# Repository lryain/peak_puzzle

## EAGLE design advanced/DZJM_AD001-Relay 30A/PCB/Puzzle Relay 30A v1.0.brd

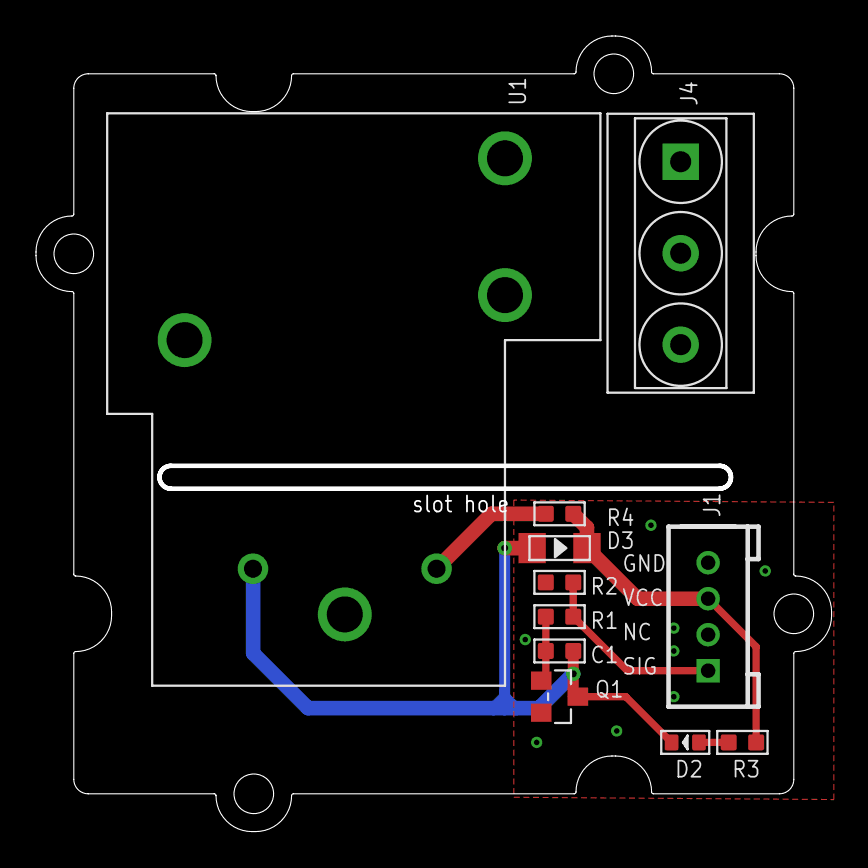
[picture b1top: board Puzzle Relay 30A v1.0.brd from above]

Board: 2 copper layers, 44.2 x 44.2 mm, 14 parts (1 on the bottom side), 10 nets.

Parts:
C1: 100pF; C0603
D2: Green; LED-0603
D3: LL4148; DO-35-SMD
J1: 4P-2.0
J4: 3P-5.08
Q1: S9013; SOT23
R1: 2k; R0603
R2: 10K; R0603
R3: 1K; R0603
R4: 10; R0603
U1: 6P-19.8H
U$3: 2X2U-DIM-W/-DRILL
U$4: OSHW_FILLX200_NOTEXT
U$6: BRICK-LOGO-2-B-MIL-0.3

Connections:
COM: J4.3, U1.4
GND: J1.4, Q1.2, R2.1
unnamed: C1.1, Q1.1, R1.2
unnamed: D2.+, R3.2
unnamed: C1.2, D2.-, D3.A, Q1.3, U1.3
unnamed: R4.2, U1.1
NC: J4.1, U1.5
NO: J4.2, U1.6
SIG: J1.1, R1.1, R2.2
VCC: D3.C, J1.3, R3.1, R4.1

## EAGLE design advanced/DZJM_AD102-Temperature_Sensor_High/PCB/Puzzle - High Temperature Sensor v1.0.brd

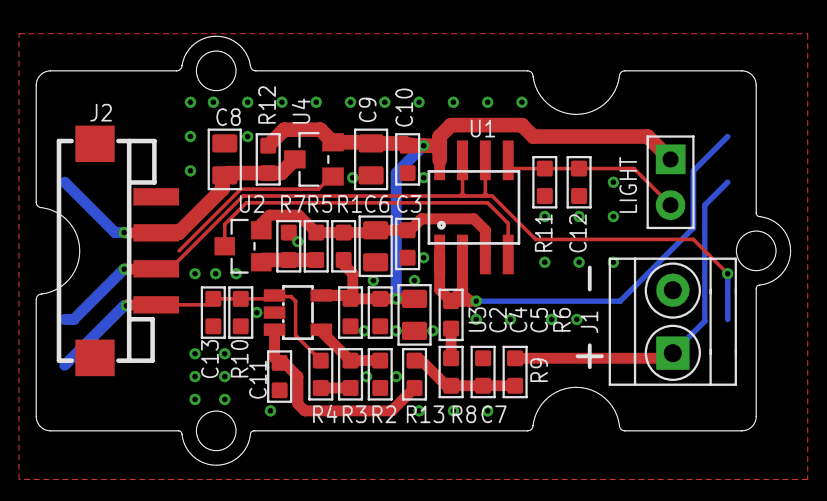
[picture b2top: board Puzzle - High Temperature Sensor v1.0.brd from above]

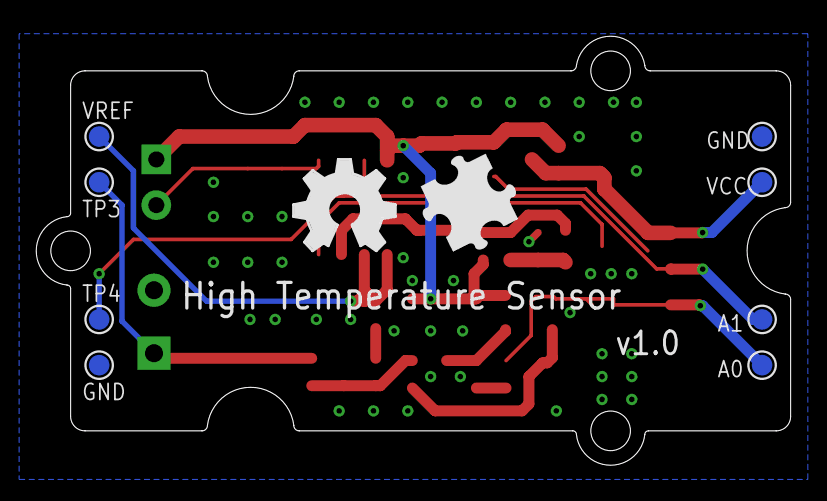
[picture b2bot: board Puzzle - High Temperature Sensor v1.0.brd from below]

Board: 2 copper layers, 41.9 x 23.8 mm, 43 parts (10 on the bottom side), 15 nets.

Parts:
A0, A1: TP3; TP_4545
C2, C3, C4, C7, C10: 100nF; C0603
C5, C6, C8, C9: 10uF/25v; C0805
C11: DNP; C0603
C12, C13: 1nF; C0603
J1: 2P-3.5
J2: Grove con; 4P-SMD-2.0
LIGHT: TTC3A103*39H; CK_1*2
R1: 330R; R0603
R2, R9: 1K_1%; R0603
R3: 51K_1%; R0603
R4: 2.4K_1%; R0603
R5: 2K_1%; R0603
R6: 150K_1%; R0603
R7, R11: 10K_1%; R0603
R8: 82K_1%; R0603
R10: 10K; R0603
R12: DNP; R0603
R13: 0R; R0603
TP, TP2, TP3, TP4: TP_4545
U1: LMV358D; SO08
U2: CJ432; SOT23
U3: OPA333DBV; SOT23-5
U4: XC6206P332MR-G; SOT23
U$9: GROVE-2CONNECTOR-SMD
U$11: BRICK-LOGO-MIL-0.6
U$12: OSHW_FILLX200_NOTEXT
VCC: TP2; TP_4545
VREF: TP4; TP_4545

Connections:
1V5: R6.2, U1.1, U1.2, VREF.T
A0: A0.T, C13.2, J2.1, R4.1, R10.2, U3.1
A1: A1.T, J2.2, TP4.T, U1.6, U1.7
GND: C2.1, C3.1, C4.1, C5.1, C6.1, C7.1, C8.1, C9.1, C10.1, C11.1, C12.1, C13.1, J1.2, J2.4, J2.SS1, J2.SS2, R2.2, R7.2, R10.1, R11.1, TP.T, TP2.T, U1.4, U2.3, U3.2, U4.1
unnamed: C7.2, R8.1, R9.2, R13.2
unnamed: R2.1, R3.2, U3.4
unnamed: J1.1, R9.1, TP3.T
unnamed: R3.1, R4.2
unnamed: C12.2, LIGHT.2, R11.2, U1.5
unnamed: R6.1, R8.2
unnamed: C11.2, R13.1, U3.3
unnamed: R5.2, R7.1, U2.1
VCC: C8.2, J2.3, R12.1, U4.3, VCC.T
VCC_3V3: C2.2, C4.2, C5.2, C9.2, C10.2, LIGHT.1, R1.1, R12.2, U1.8, U3.5, U4.2
VREF: C3.2, C6.2, R1.2, R5.1, U1.3, U2.2

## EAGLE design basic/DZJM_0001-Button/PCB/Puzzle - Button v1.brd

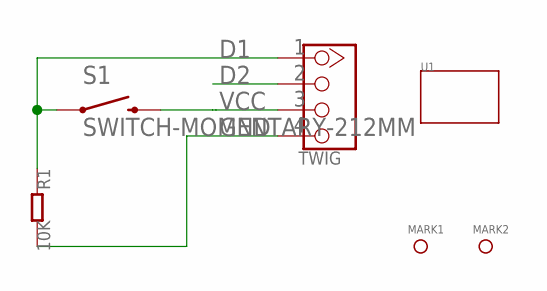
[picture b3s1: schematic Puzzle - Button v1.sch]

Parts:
J1: TWIG; 4P-LEADED-2.0
MARK1, MARK2: PAD-MARK; ROUND-MARK-0.635
R1: 10K; 0603
S1: SWITCH-MOMENTARY-212MM; TACTILE-PTH-12MM
U1: TWIG-1U; 1U-DIM-W/-DRILL

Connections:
D1: J1.1, R1.1, S1.1
D2: J1.2
GND: J1.4, R1.2
VCC: J1.3, S1.3 (2)

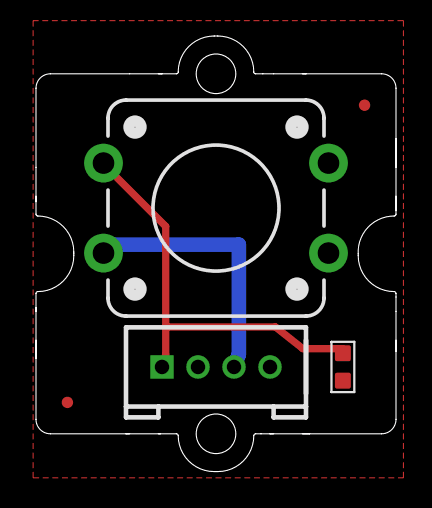
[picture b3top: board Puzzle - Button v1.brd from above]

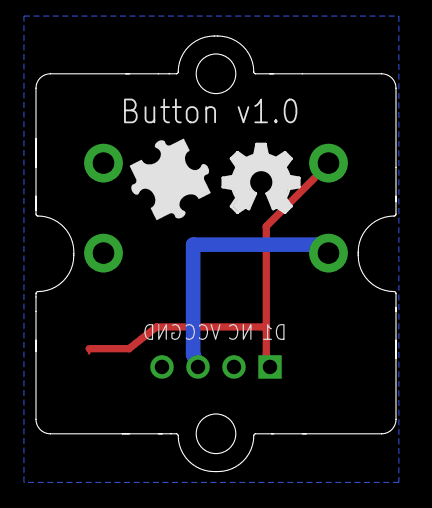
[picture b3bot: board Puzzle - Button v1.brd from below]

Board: 2 copper layers, 20.0 x 24.2 mm, 8 parts (2 on the bottom side), 3 nets.

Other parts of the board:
LOGO2: LOGO-OSHW-FILLX0150-NT; OSHW_FILLX150_NOTEXT
U$1: BRICK-LOGO-MIL-0.5

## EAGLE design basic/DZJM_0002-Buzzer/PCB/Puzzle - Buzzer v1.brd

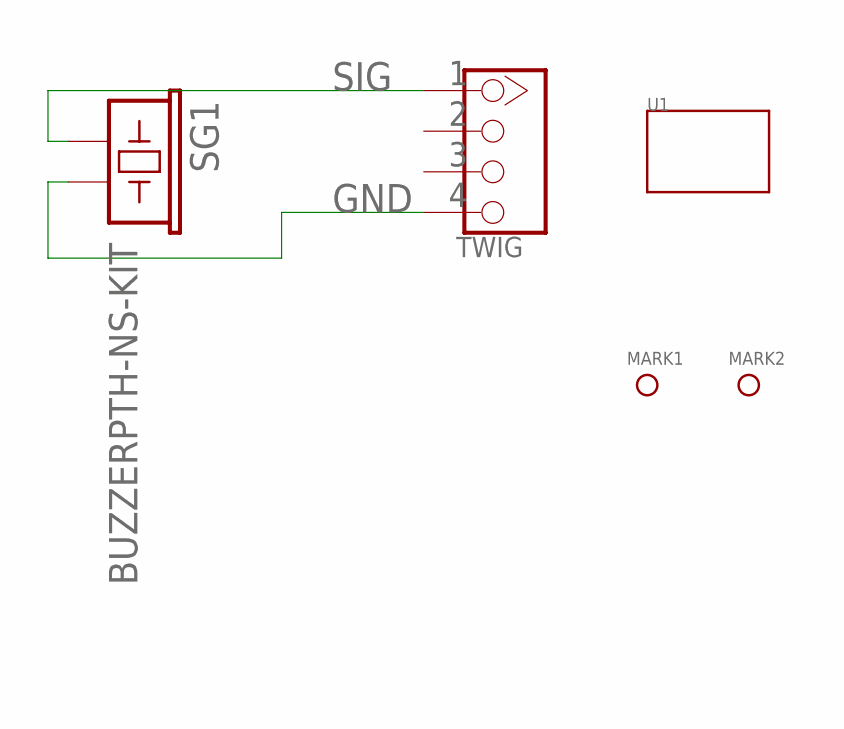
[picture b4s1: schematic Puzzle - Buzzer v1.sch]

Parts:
J1: TWIG; 4P-LEADED-2.0
MARK1, MARK2: PAD-MARK; ROUND-MARK-0.635
SG1: BUZZERPTH-NS-KIT; BUZZER-12MM-NS-KIT
U1: TWIG-1U; 1U-DIM-W/-DRILL

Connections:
GND: J1.4, SG1.- (2)
SIG: J1.1, SG1.+ (1)

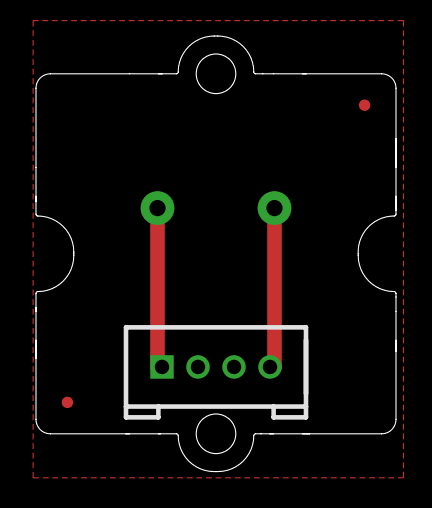
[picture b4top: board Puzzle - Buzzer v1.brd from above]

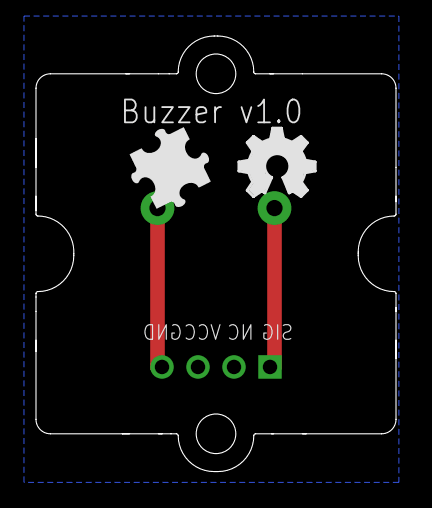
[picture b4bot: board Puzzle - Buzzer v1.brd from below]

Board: 2 copper layers, 20.0 x 24.2 mm, 7 parts (2 on the bottom side), 2 nets.

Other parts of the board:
U$1: BRICK-LOGO-MIL-0.5
U$2: OSHW_FILLX150_NOTEXT_S

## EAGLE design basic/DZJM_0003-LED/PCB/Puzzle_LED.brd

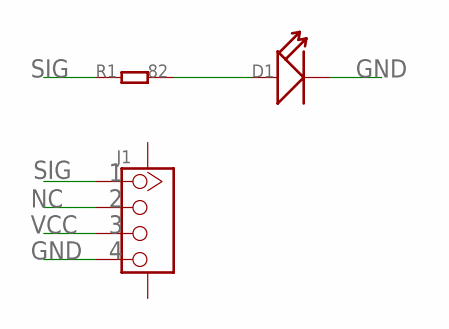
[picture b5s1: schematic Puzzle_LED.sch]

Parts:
D1: LED-6MM; LED-2P-2.54-6MM
J1: TWIG-4P-2.0-SMD-FEMALE-REINFORCE'90D'; 4P-SMD-2.0-90D
R1: 82; 0603

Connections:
GND: D1.-, J1.4
unnamed: D1.+, R1.2
NC: J1.2
SIG: J1.1, R1.1
VCC: J1.3

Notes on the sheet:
SIG
GND
VCC

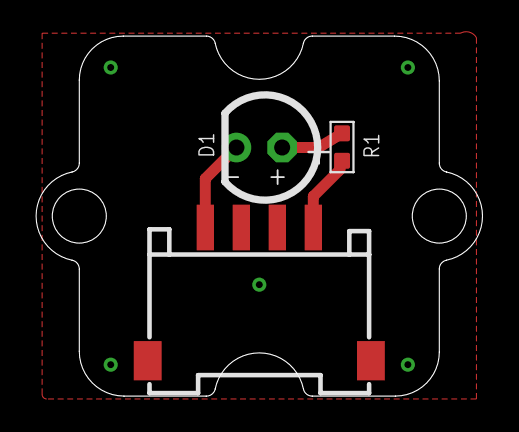
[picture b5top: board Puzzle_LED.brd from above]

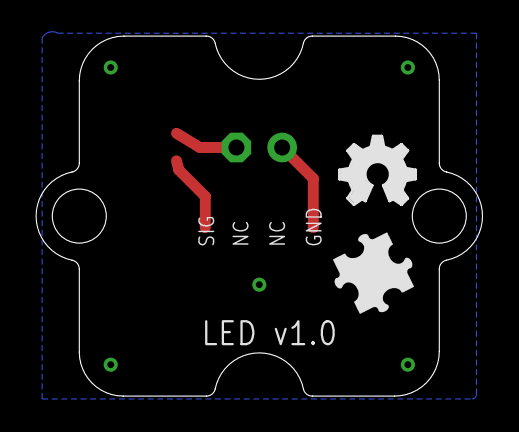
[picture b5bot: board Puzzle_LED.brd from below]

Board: 2 copper layers, 24.8 x 20.0 mm, 6 parts (2 on the bottom side), 3 nets.

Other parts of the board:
U$2: BRICK-LOGO-MIL-0.5
U$3: OSHW_FILLX150_NOTEXT_S
U$4: DZJM-B20-1P

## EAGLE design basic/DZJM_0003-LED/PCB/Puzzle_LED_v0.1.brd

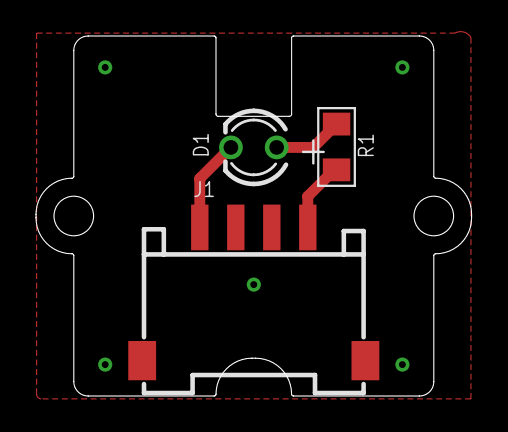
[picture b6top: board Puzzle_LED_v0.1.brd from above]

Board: 2 copper layers, 24.2 x 20.0 mm, 4 parts (0 on the bottom side), 3 nets.

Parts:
D1: LED-2P-2.54-3MM
J1: 4P-SMD-2.0-90D
R1: 82; 1206
U$1: 1U-DIM

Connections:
GND: D1.K, J1.4
unnamed: D1.A, R1.2
SIG: J1.1, R1.1

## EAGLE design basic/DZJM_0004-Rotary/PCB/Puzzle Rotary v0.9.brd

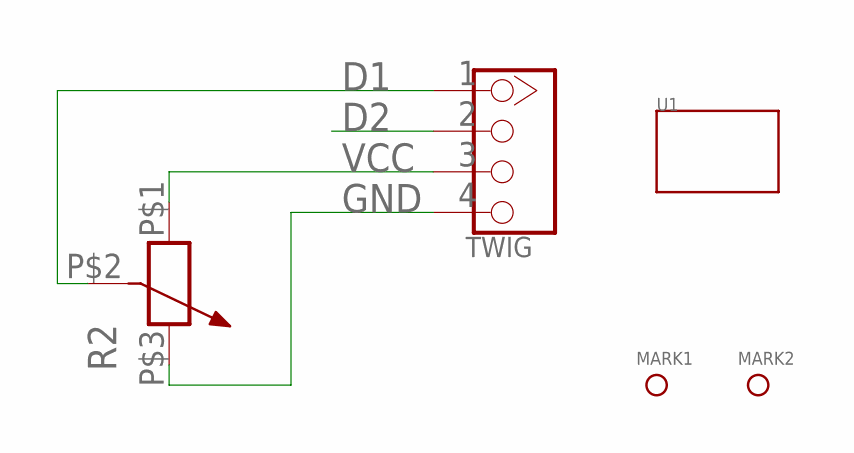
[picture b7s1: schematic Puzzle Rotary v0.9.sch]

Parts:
J1: TWIG; 4P-LEADED-2.0
MARK1, MARK2: PAD-MARK; ROUND-MARK-0.635
R2: R-POTENTIOMETER-ALPS-POT; 3P-SQUA-13.6X12.4
U1: TWIG-1U; 1U-DIM-W/-DRILL

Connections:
D1: J1.1, R2.P$2 (3)
D2: J1.2
GND: J1.4, R2.P$3 (2)
VCC: J1.3, R2.P$1 (1)

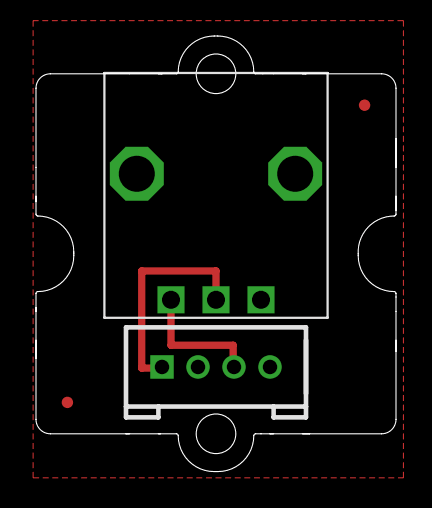
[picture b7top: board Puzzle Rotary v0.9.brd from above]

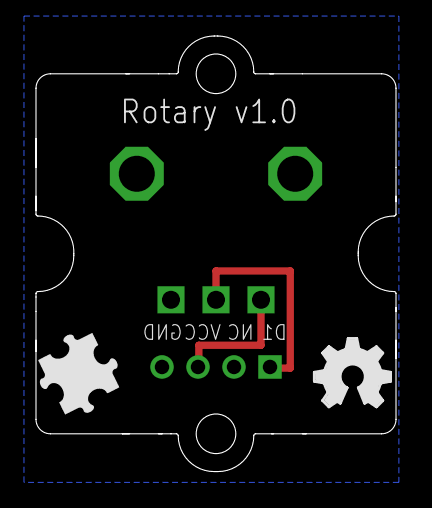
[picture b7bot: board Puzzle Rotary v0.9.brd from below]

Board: 2 copper layers, 20.0 x 24.2 mm, 7 parts (2 on the bottom side), 3 nets.

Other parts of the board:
LOGO2: LOGO-OSHW-FILLX0150-NT; OSHW_FILLX150_NOTEXT
U$1: BRICK-LOGO-MIL-0.5

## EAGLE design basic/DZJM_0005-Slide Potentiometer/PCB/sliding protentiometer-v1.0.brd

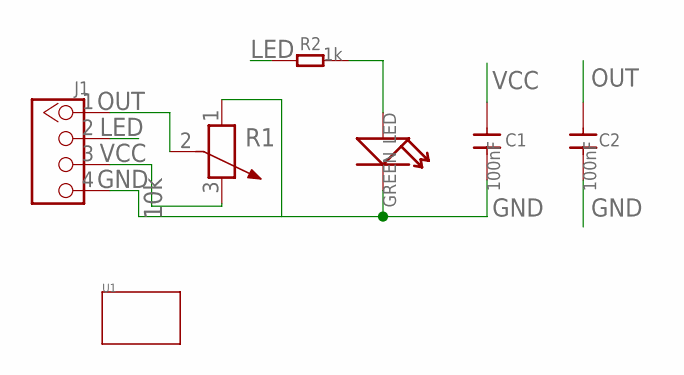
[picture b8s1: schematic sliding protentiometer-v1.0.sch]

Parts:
C1, C2: 100nF; 0805
J1: TWIG-4P-2.0-2.0; 4P-2.0
LED: GREEN; LED-0805
R1: 10k; 3P-SQUA-45.6X10X5.8H
R2: 1k; 0805
U1: TWIG'3U'; 3U-DIM-W/-DRILL

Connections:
GND: C1.2, C2.2, J1.4, LED.-, R1.1
LED: J1.2, R2.1
unnamed: LED.+, R2.2
OUT: C2.1, J1.1, R1.2 (3)
VCC: C1.1, J1.3, R1.3 (2)

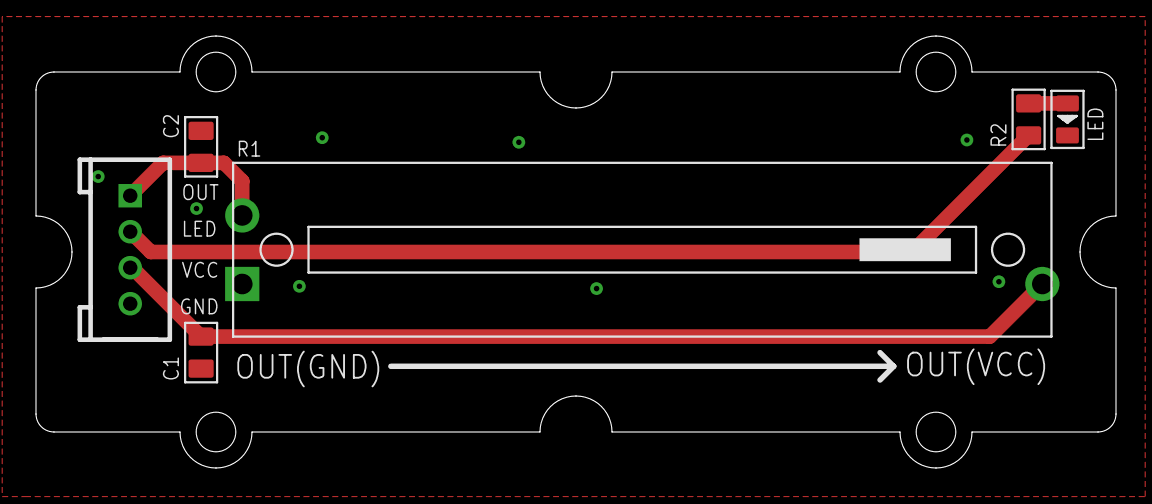
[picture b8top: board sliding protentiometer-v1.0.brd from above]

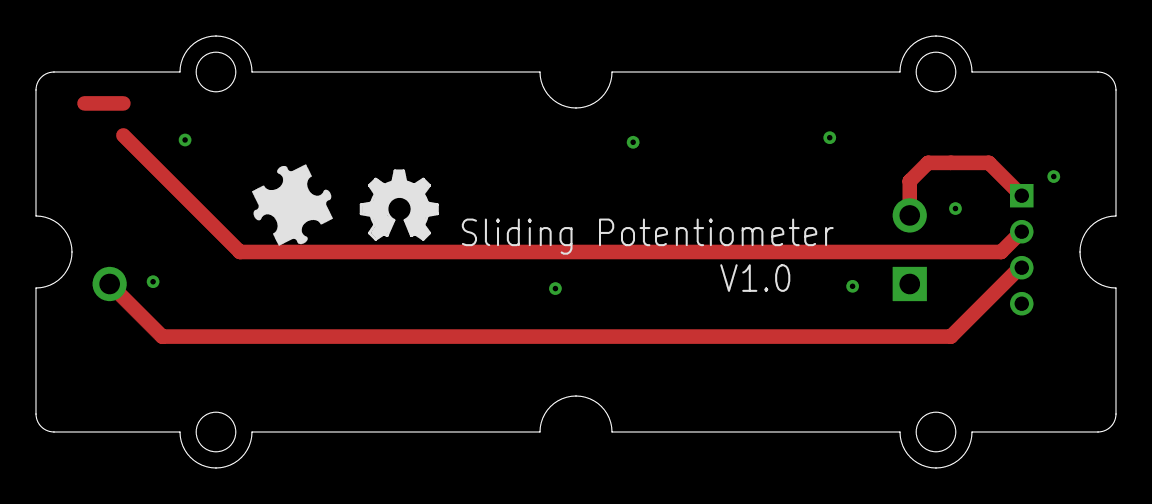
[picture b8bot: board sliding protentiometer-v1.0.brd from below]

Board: 2 copper layers, 60.0 x 24.0 mm, 9 parts (2 on the bottom side), 5 nets.

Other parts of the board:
U$1: BRICK-LOGO-MIL-0.5
U$2: OSHW_FILLX150_NOTEXT

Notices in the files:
parts and their libraries:
SparkFun: Licensing: CC v3.0 Share-Alike You are welcome to use this library for commercial purposes.
